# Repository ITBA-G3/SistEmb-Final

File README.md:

# SistEmb-Final

**Trabajo Práctico Final — Sistemas Embebidos (25.27)**  
Instituto Tecnológico de Buenos Aires (ITBA)

Repositorio del proyecto final de la materia **Sistemas Embebidos**, que implementa un **reproductor de audio embebido** sobre una MCU, con manejo de periféricos reales, multitarea con RTOS e interfaz de usuario.

## Descripción general

El proyecto consiste en el desarrollo de un **reproductor de música embebido**, capaz de leer archivos desde una **tarjeta SD**, reproducir audio y permitir la interacción del usuario mediante **encoder rotatorio, botones y display I2C**.

La lógica principal está organizada como una **máquina de estados**, ejecutada dentro de una *task* del sistema operativo en tiempo real.

##  Funcionalidades principales

- Lectura de archivos de audio desde **SD Card**
- Reproducción de audio mediante periféricos dedicados
- Control de reproducción:
  - Play
  - Pause
  - Cambio de canción
- Interfaz de usuario:
  - Encoder rotatorio para navegación
  - Botones de control
  - Display I2C para mostrar estado e información
- Arquitectura multitarea basada en **RTOS (µC/OS)**

##  Máquina de estados

La *task* principal implementa una **FSM (Finite State Machine)** con tres estados:

- **MENU**
  - Navegación entre canciones mediante el encoder
  - Selección de canción
- **PLAY**
  - Reproducción activa
  - Cambio de canción sin salir del estado
  - Opción de pausar o volver al menú
- **PAUSE**
  - Reproducción pausada
  - Reanudar reproducción
  - Volver al menú

## Autores

- Diaz Guzmán, Ezequiel.
- Hertter, José Iván.
- Ruíz, Lucía Inés.
- Meichtry, Cristian Damián.

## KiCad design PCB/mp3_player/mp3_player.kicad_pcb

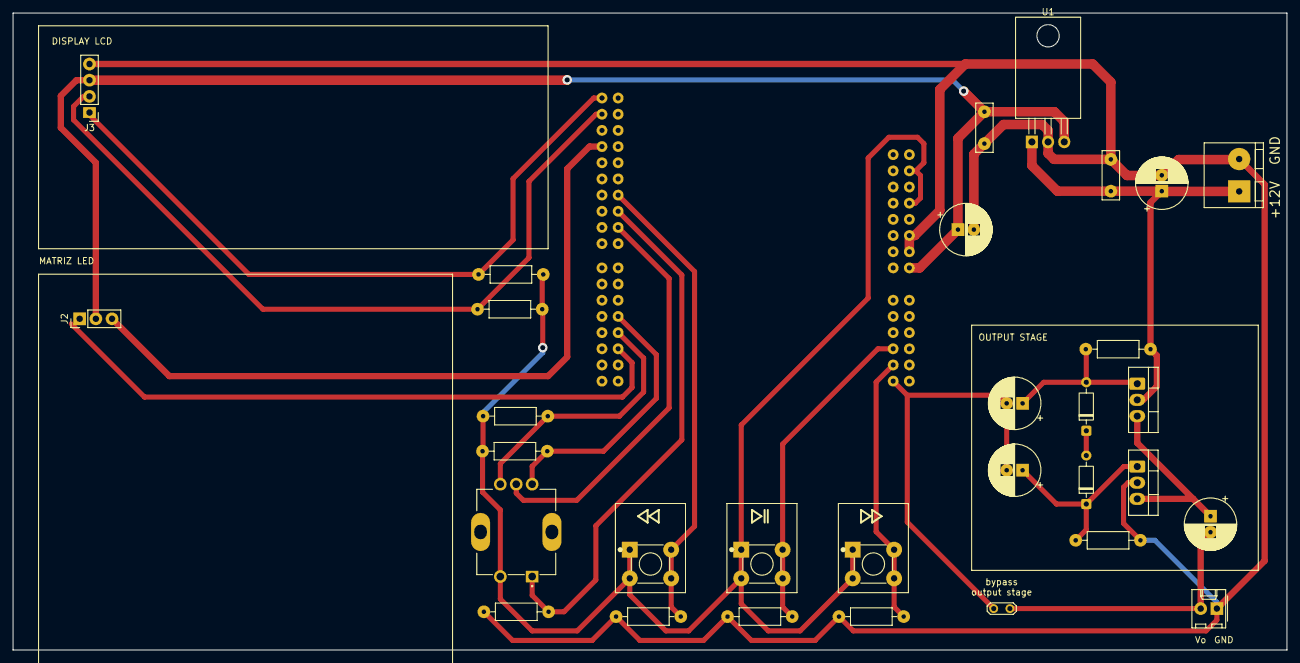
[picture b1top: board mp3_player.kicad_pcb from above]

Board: 2 copper layers, 200.0 x 100.0 mm, 32 parts (1 on the bottom side), 19 nets.

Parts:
C1, C2: C; C_5mm
C3, C4, C5, C6, C7: C_Polarized; CP_2.50mm
D1, D2: 1N4148; D_DO-35_SOD27_P7.62mm_Horizontal
J1: FRDM-K64F
J2: Conn_01x03_Pin; PinHeader_1x03_P2.54mm_Vertical
J3: Conn_01x04_Pin; PinHeader_1x04_P2.54mm_Vertical
J4: Terminal_2; Bornera_2_P5mm
J7: Connector_2_Pol; Molex_1x02_P2.54mm
JP1: Jumper_2_Bridged; TestPoint_2Pads_Pitch2.54mm_Drill0.8mm
Q1: TIP32; TO-220-3_Vertical
Q2: TIP31; TO-220-3_Vertical
R1, R2: 10k; R_0.25W
R3, R4, R10, R11: R; R_0.25W
R5, R6, R7, R8: 1k; R_0.25W
S1, S2, S3: SW_Tactile
SW1: RotaryEncoder_Switch; XDCR_PEC12R-4115F-S0012
U1: L7805; TO-220-3_Horizontal_TabDown

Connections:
+3V3: J1.J3-4 (P3V3_1), J1.J3-8 (P3V3_2), R1.1, R2.2, R3.1, R4.1, S1.1, S1.2, S2.1, S2.2, S3.1, S3.2, SW1.S2
+5V: C1.1, C3.1, J1.J3-16 (P5-9V_VIN), J2.2, J3.3, U1.3 (OUT)
+12V: C2.1, C4.1, J4.2, Q2.2 (C), R11.1, U1.1 (IN)
/DAC_out: C6.2, C7.2, J1.J4-11 (DAC0_OUT), JP1.1 (A)
/bt_next: J1.J4-9 (PTB20), R6.1, S2.3, S2.4
/bt_play/stop: J1.J4-7 (ADC1_DM1), R5.1, S1.3, S1.4
/bt_prev: J1.J2-7 (ADC0_DM0), R7.1, S3.3, S3.4
/enc_RCHA: J1.J1-9 (PTC9), R2.1, SW1.A
/enc_RCHB: J1.J1-7 (PTC8), R1.2, SW1.B
/enc_sw: J1.J2-5 (ADC0_DP0), R8.1, SW1.S1
/etapa_salida: C5.2, J7.2, JP1.2 (B)
/matriz_led: J1.J1-5 (PTC1), J2.1
/scl: J1.J2-20 (PTE24), J3.1, R4.2
/sda: J1.J2-18 (PTE25), J3.2, R3.2
GND: C1.2, C2.2, C3.2, C4.2, J1.J2-3 (GND0), J1.J2-14 (GND1), J1.J3-12 (GND2), J1.J3-14 (GND3), J2.3, J3.4, J4.1, J7.1, Q1.2 (C), R5.2, R6.2, R7.2, R8.2, R10.2, SW1.C, U1.2 (GND)
unnamed: C6.1, D1.2 (A), Q2.1 (B), R11.2
unnamed: D1.1 (K), D2.2 (A)
unnamed: C7.1, D2.1 (K), Q1.1 (B), R10.1
unnamed: C5.1, Q1.3 (E), Q2.3 (E)

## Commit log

2024-12-22 creacion de proyecto (base tp4 con RTOS) y consigna
2024-12-22 configuración inicial de proyecto vacío
2025-05-14 README update: division de tareas
2025-05-19 Borrón y cuenta nueva de encoder. Ya hay interrupciones.
2025-05-19 Agregue funciones
2025-05-19 CM se asigno el vumetro
2025-05-19 Project Setup: - Non RTOS - Drivers included: Should be checked. DMA FTM PISR PWM: uses DMA and FTM UART: has 2 warnings in DJacoby files, ignore.
2025-05-19 helix mp3 decoder file added
2025-05-19 borre FTM y PWM, por ahora no los necesitamos
2025-05-19 up to date with main, avoid future merge conflicts :)
2025-05-19 Encoder con funciones e IRQ
2025-05-20 inicios de vumetro
2025-05-20 Discretización de frecuencias y niveles de volumen
2025-05-21 comentarios en las funciones de discretización
2025-06-02 Inicio de driver de micro SD + FAT
2025-06-02 minuta 1
2025-06-09 Avances en vumetro y matriz
2025-11-04 FTM ok
2025-11-10 driver led matrix estructurado, hay un bug raro de timing, prox iteración con dma para cumplir tiempos
2025-12-02 Led Matrix with DMA. Continue testing, bug with rox 8
2025-12-02 bug fix hardcodeado
2025-12-02 added pit support for 10fps
2025-12-02 vumeter/spectrogram control
2025-12-03 feat: firt functional version of LCD. Error on shift function when text is shorter than DISPLAY_WIDTH
2025-12-06 add encoder driver - NOT TESTED
2025-12-06 refine code - compiles but not tested
2025-12-06 pusheo esto pero no se si es necesario
2025-12-07 no anda, pero lo emprolijé
2025-12-10 Test en el que funciona el driver de encoder.
2025-12-11 cambios, avances, compila y no funciona.
2025-12-12 feat: project & libraries created
2025-12-12 feat: add .gitignore
2025-12-12 feat: esquematico listo para revisar
2025-12-12 feat: PCB ready
2025-12-12 SD initialization complete
2025-12-12 intento de hacer transfer con adma
2025-12-13 fix: SD card initialized, written and read
2025-12-13 feat: se puede escribir en ambas lineas. Admite sobreescribir. Hay un error en shift
2025-12-13 feat: Filesystem working
2025-12-13 feat: Helix mp3 library added
2025-12-13 feat: word shift now working
2025-12-13 Critical: Takes too long to complete one loop. Implement DMA as soon as possible
2025-12-14 initial PIT triggered DMA DAc transfer OK
2025-12-15 now DMA IRQ are firing
2025-12-15 ping pong buffer implemented and tested for dac output
2025-12-16 creeeeo que fft y visualización andando ok. seguir testeando
2025-12-17 app skeleton (not compiled yet)
2025-12-17 add header files
2025-12-18 documentation
2025-12-18 fft with cmsis-dsp arm module
2025-12-18 energy in band instead of power density
2025-12-18 audio and spectrogram tests in /Tests/, can copy and paste to app.c to run
2025-12-19 arreglos al dac, saltos por pingpong buffer
2025-12-19 left sd test in folder tests
2025-12-19 moved main to test_LCD
2025-12-19 inclui ucosii. ahora compila.
2025-12-19 se me crashea mcu :(
2025-12-19 Audio task created, working ok. Led Matrix task created, not working.
2025-12-20 anda, tiene un glitch que falta resolver
2025-12-20 fix: habia conflicto con pisr nuestro y con el de ucosii
2025-12-20 glitch que no entiendo
2025-12-20 glitch arreglado
2025-12-20 glitch arreglado y algo que no pushie
2025-12-20 add FSM with transitions only (no tasks)
2025-12-21 Error en interrupciones. Supuestamente es de UART pero no esta agregado UART
2025-12-21 fix: no habia handlers para PITn n>1
2025-12-21 fix: funcionan los gpios
2025-12-21 fix: button recognition
2025-12-21 refine FSM
2025-12-21 add buttons/encoder events and refine FSM
2025-12-21 ahora compila, inclui encoder.h
2025-12-21 feat: .gitignore updated
2025-12-21 probar si funciona la salida de mp3
2025-12-21 hay un problema con la inicializacion del I2C. Creo que es por los delays que se usan con RTOS
2025-12-21 updated gitignore
2025-12-21 parece andar el audio
2025-12-21 aumento de buffer para que no suene lento
2025-12-22 probalo eze
2025-12-22 probá eze 2
2025-12-22 eze proba, no se si compila se murio mcu
2025-12-22 agregue un pend que faltaba en audio task
2025-12-22 audiofillsem
2025-12-22 fix: se cambio el driver de I2C para arreglar el bug del LCD
2025-12-22 checkpoint. Se escucha a velocidad casi normal, pero tiene cortes
2025-12-22 test eze
2025-12-22 fix: problema en el armado de frames, hice un pulso de 3 mensajes i2c para cada letra así hay un pulso entero de EN
2025-12-22 Se agregaron protecciones a los punteros write y read del ring buffer. Ya no se esccuchan duplicados los frames
2025-12-22 funciona el audio a 22kHz
2025-12-22 version presentable. Bug: solo reproduce la primera cancion
2025-12-22 feat: se agrego un ecualizador estatico
2025-12-22 feat: debouncing boton
2025-12-22 Version presentable
2025-12-22 acomodar un poco el repo para presentar
